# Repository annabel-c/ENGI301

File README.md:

# ENGI301

Repository for ENGI301 coursework

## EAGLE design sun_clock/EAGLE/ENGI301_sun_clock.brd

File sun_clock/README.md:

# PCB: PocketBeagle Sun Clock
Clock that shows the position of the sun and has a screen display of time; alarm can be set through mode, hour, and minute buttons.
This is a PCB design based on the PocketBeagle Sun Clock. See "https://github.com/annabel-c/ENGI301/tree/master/project_01" for original project.

## Files
Schematic

Board/Layout

Gerbers

Bill-of-Materials

Additional Documentation

## Story
When times call for another alarm clock--why not build it yourself? Make it fun with your personal indoor sun and moon (great for a cloudy day!), and have the option to set an alarm through 3 simple buttons: mode, hour and minute.

## Overview

The TFT display shows the time. Time is set upon boot, in Central Standard Time. Hold down the mode button (blue) to set an alarm time with hour (yellow) and minute (red). Every press increments the respective parameter by 1. Press hour and minute buttons at the same time to toggle alarm on and off. The on state is indicated by a red border (replacing the original gray one) on the screen display. A buzzer will sound at the time of the alarm, lasting a few seconds and turning off automatically. The servo will rotate 180 degrees at 6 am and 6 pm, revealing the sun or moon representing daytime or nighttime, respectively.

## Instructions

#### Hardware

The main pin configurations are described below:

TFT screen - SPI0

RTC - I2C1

Servo - PWM0

Speaker - PWM1

Buttons - GPIO 64, 46, 48

### Software

For help getting started with a PocketBeagle, see https://beagleboard.org/getting-started. Before running the code, several libraries must be downloaded:

- Install the Adafruit_Blinka library by running the following in Cloud9 IDE

sudo pip3 install Adafruit_Blinka

(run "sudo apt-get install python-setuptools" and "sudo apt-get install python-dev" if the above throws an error)

and download the Adafruit CircuitPython Library Bundle at https://github.com/adafruit/Adafruit_CircuitPython_Bundle

- Follow the instructions at https://learn.adafruit.com/adafruit-2-dot-8-color-tft-touchscreen-breakout-v2/python-wiring-and-setup for installing the RGB Display Library, DejaVu TTF Font, and the Pillow Library

See the Hackster.io page for more details: https://www.hackster.io/annabel-chang/pocketbeagle-sun-clock-f72acc

In the process of coding, make sure to use python3 (instead of python) is and use the prefix "sudo" to resolve any permission issues.

With everything set up, running

sudo python3 sun_clock.py

in the current directory should produce the clock display and functions as described in the first section. An auto run is also set up for this project such that the file runs upon boot, given in run.sh.

A video demonstrating how the alarm works can be reached here: https://www.youtube.com/watch?v=hUiSdnFPSFs&feature=youtu.be

In the video, the current time is 03:22, the alarm is set to 03:23 by holding the mode button and pressing the minute button (not shown setting from the initial 00:00 due to time constraints), the alarm is turned on by pressing hour and minute together (screen border turns red), and wait.... the alarm begins beeping at the set time! The alarm eventually terminates and the gray screen border is restored.

## Future Work

The screen provides a great deal of potential and versatility for this project; a touchscreen controller can be added so that touchcreen buttons replace the physical one, or other modes such as photo galleries and temperature/humidity detection can be included within the clock.

Python code for RTC with PocketBeagle remains to be investigated, hence this iteration of this project relies on datetime for time information. Future iterations could focus more on user-setting time and mode changes.

In addition, to become a more finished, stand-alone product, the clock should have a battery instead of an USB cable, and an aesthetic casing or LED effects would put the finishing touches on it.

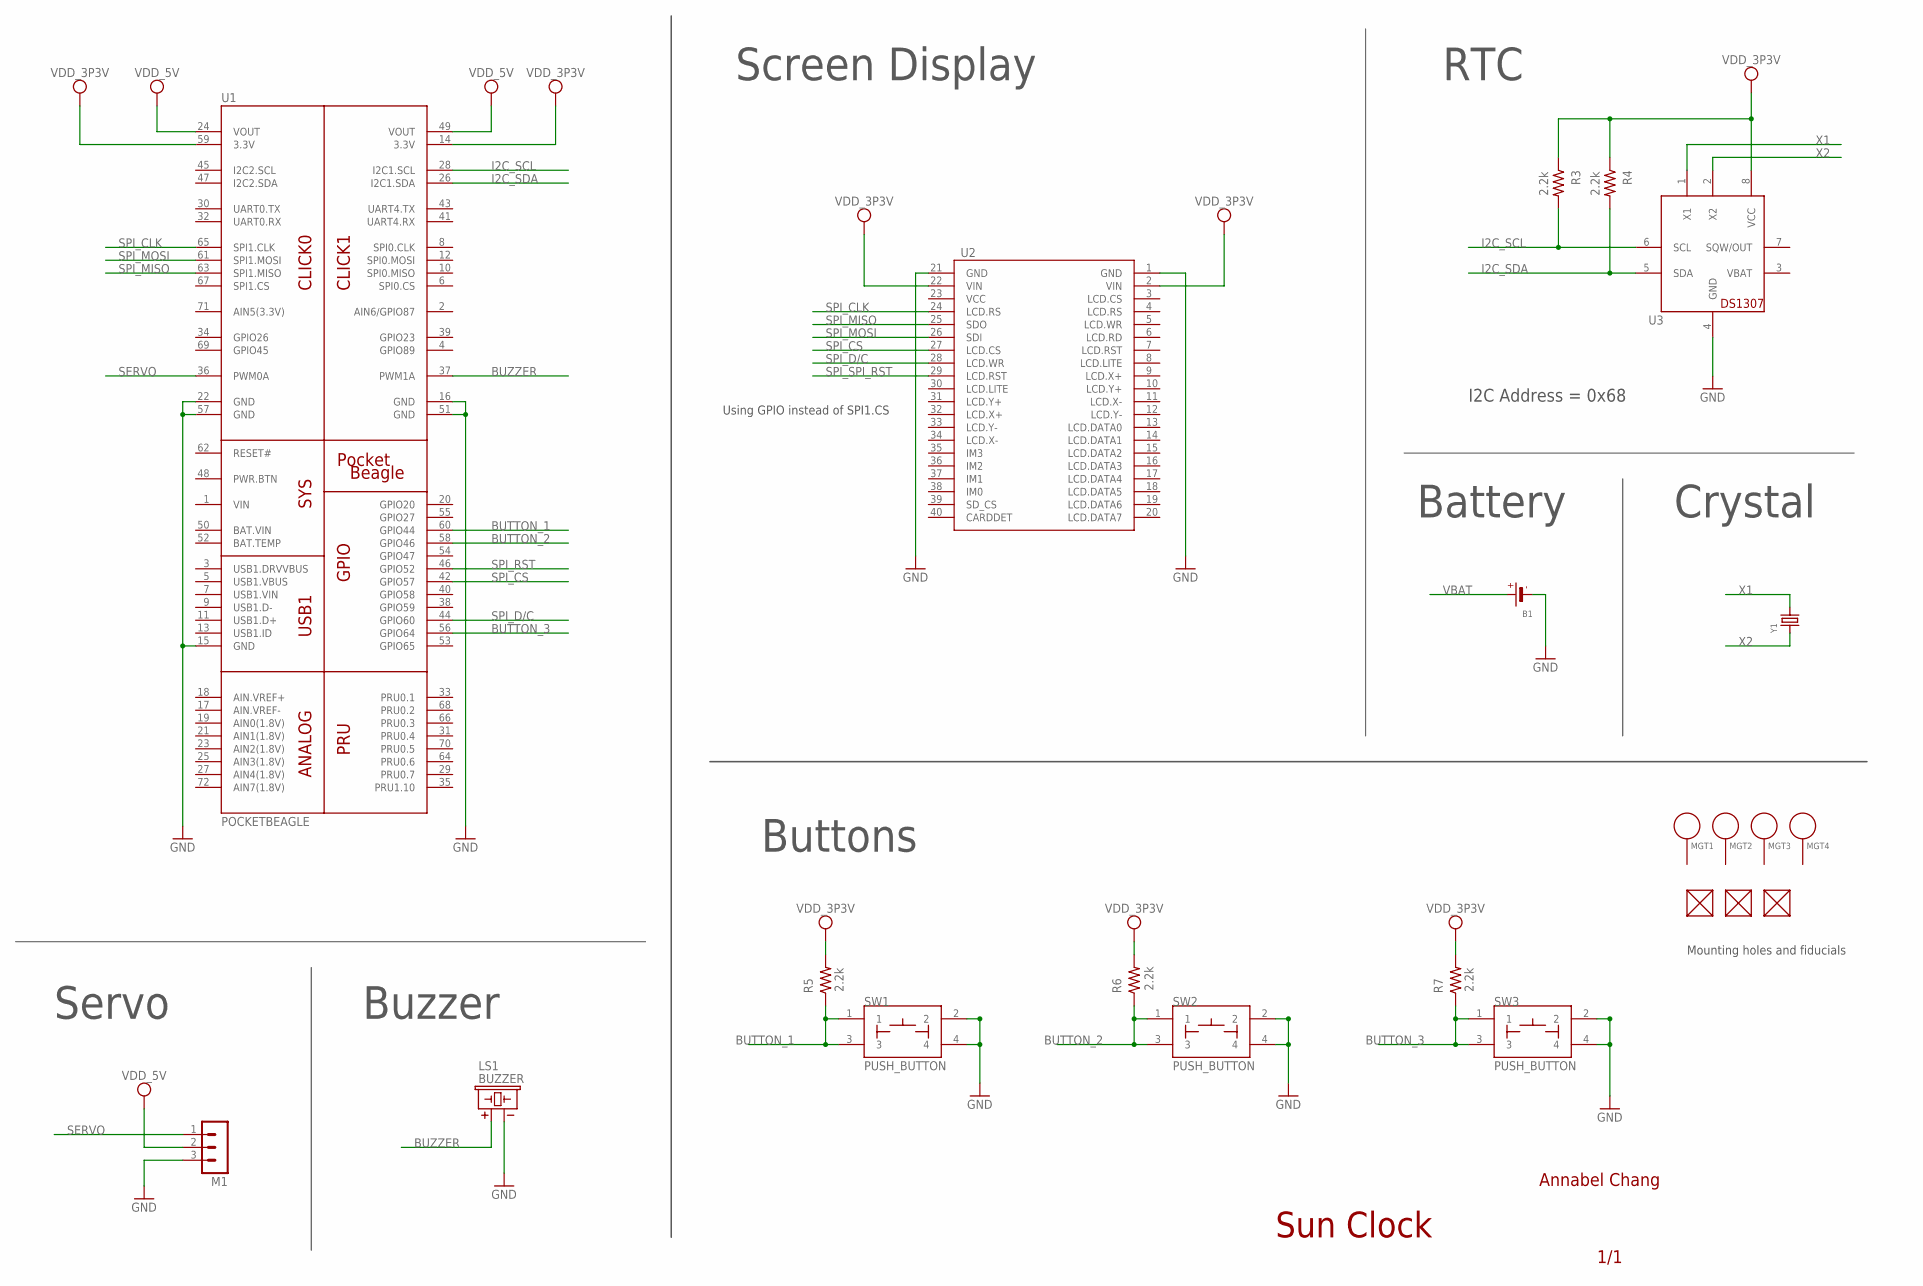
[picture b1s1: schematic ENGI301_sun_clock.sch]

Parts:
B1: BATTERYCR1220_SMT; CR1220
FUD1, FUD2, FUD3: FIDUCIAL; FIDUCIAL_40MIL
LS1: BUZZER; BUZZER_6.5MM
M1: MA03-1
MGT1, MGT2, MGT3, MGT4: MOUNTING_HOLE
R3, R4: 2.2k; R0805
R5, R6, R7: 2.2k; R0603
SW1, SW2, SW3: PUSH_BUTTON; BUTTON_12.5MM
U1: POCKETBEAGLE
U2: DISP_LCD_2.8IN
U3: DS1307; DIL08
Y1: CRYSTAL8.0X3.8; CRYSTAL_8X3.8

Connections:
BAT.VIN: U1.50 (BAT.VIN)
BUTTON_1: R5.1, SW1.1, SW1.3, U1.60 (GPIO44)
BUTTON_2: R6.1, SW2.1, SW2.3, U1.58 (GPIO46)
BUTTON_3: R7.1, SW3.1, SW3.3, U1.56 (GPIO64)
BUZZER: LS1.+, U1.37 (PWM1A)
GND: B1.-, LS1.-, M1.3, SW1.2, SW1.4, SW2.2, SW2.4, SW3.2, SW3.4, U1.15 (GND), U1.16 (GND), U1.22 (GND), U1.51 (GND), U1.57 (GND), U2.1 (GND), U2.21 (GND), U3.4 (GND)
I2C_SCL: R3.2, U1.28 (I2C1.SCL), U3.6 (SCL)
I2C_SDA: R4.2, U1.26 (I2C1.SDA), U3.5 (SDA)
SERVO: M1.1, U1.36 (PWM0A)
SPI_CLK: U1.65 (SPI1.CLK), U2.24 (LCD.RS)
SPI_CS: U1.42 (GPIO57), U2.27 (LCD.CS)
SPI_D/C: U1.44 (GPIO60), U2.28 (LCD.WR)
SPI_MISO: U1.63 (SPI1.MISO), U2.25 (SDO)
SPI_MOSI: U1.61 (SPI1.MOSI), U2.26 (SDI)
SPI_RST: U1.46 (GPIO52)
SPI_SPI_RST: U2.29 (LCD.RST)
VBAT: B1.+$1 (+), U3.3 (VBAT)
VDD_3P3V: R3.1, R4.1, R5.2, R6.2, R7.2, U1.14 (3.3V), U1.59 (3.3V), U2.2 (VIN), U2.22 (VIN), U3.8 (VCC)
VDD_5V: M1.2, U1.24 (VOUT), U1.49 (VOUT)
VIN: U1.1 (VIN)
X1: U3.1 (X1), Y1.P$4 (2)
X2: U3.2 (X2), Y1.P$1 (1)

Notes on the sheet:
Buttons
Servo
Screen Display
RTC
Buzzer
I2C Address = 0x68
Using GPIO instead of SPI1.CS
Annabel Chang
1/1
Sun Clock
Battery
Crystal
Mounting holes and fiducials

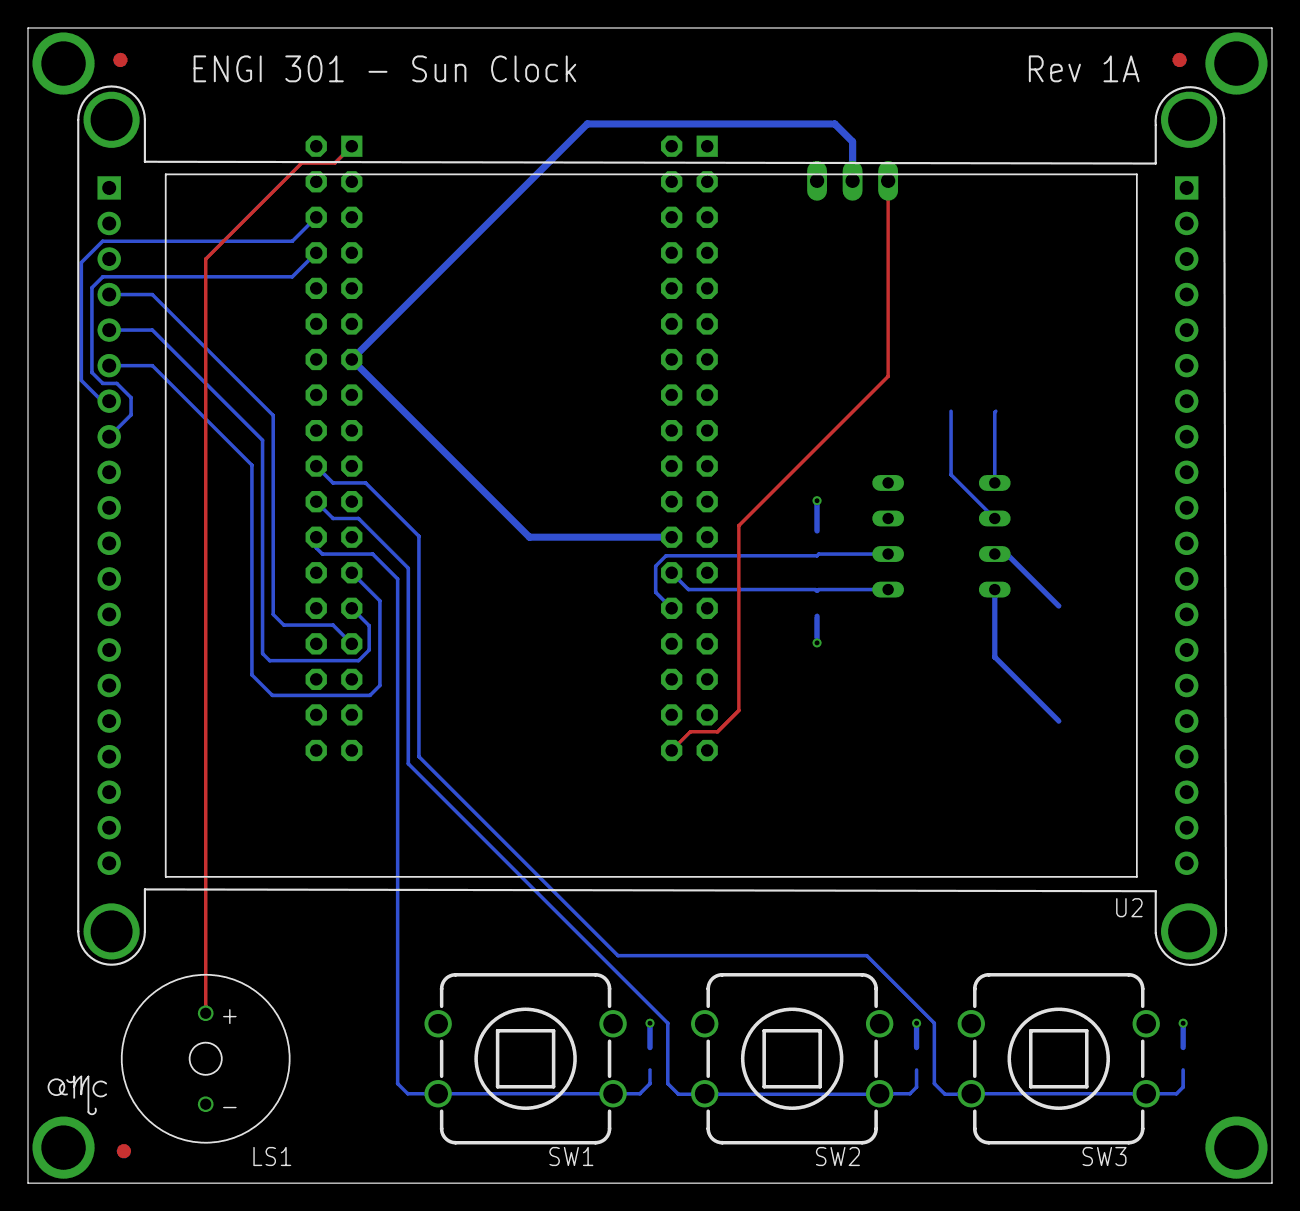
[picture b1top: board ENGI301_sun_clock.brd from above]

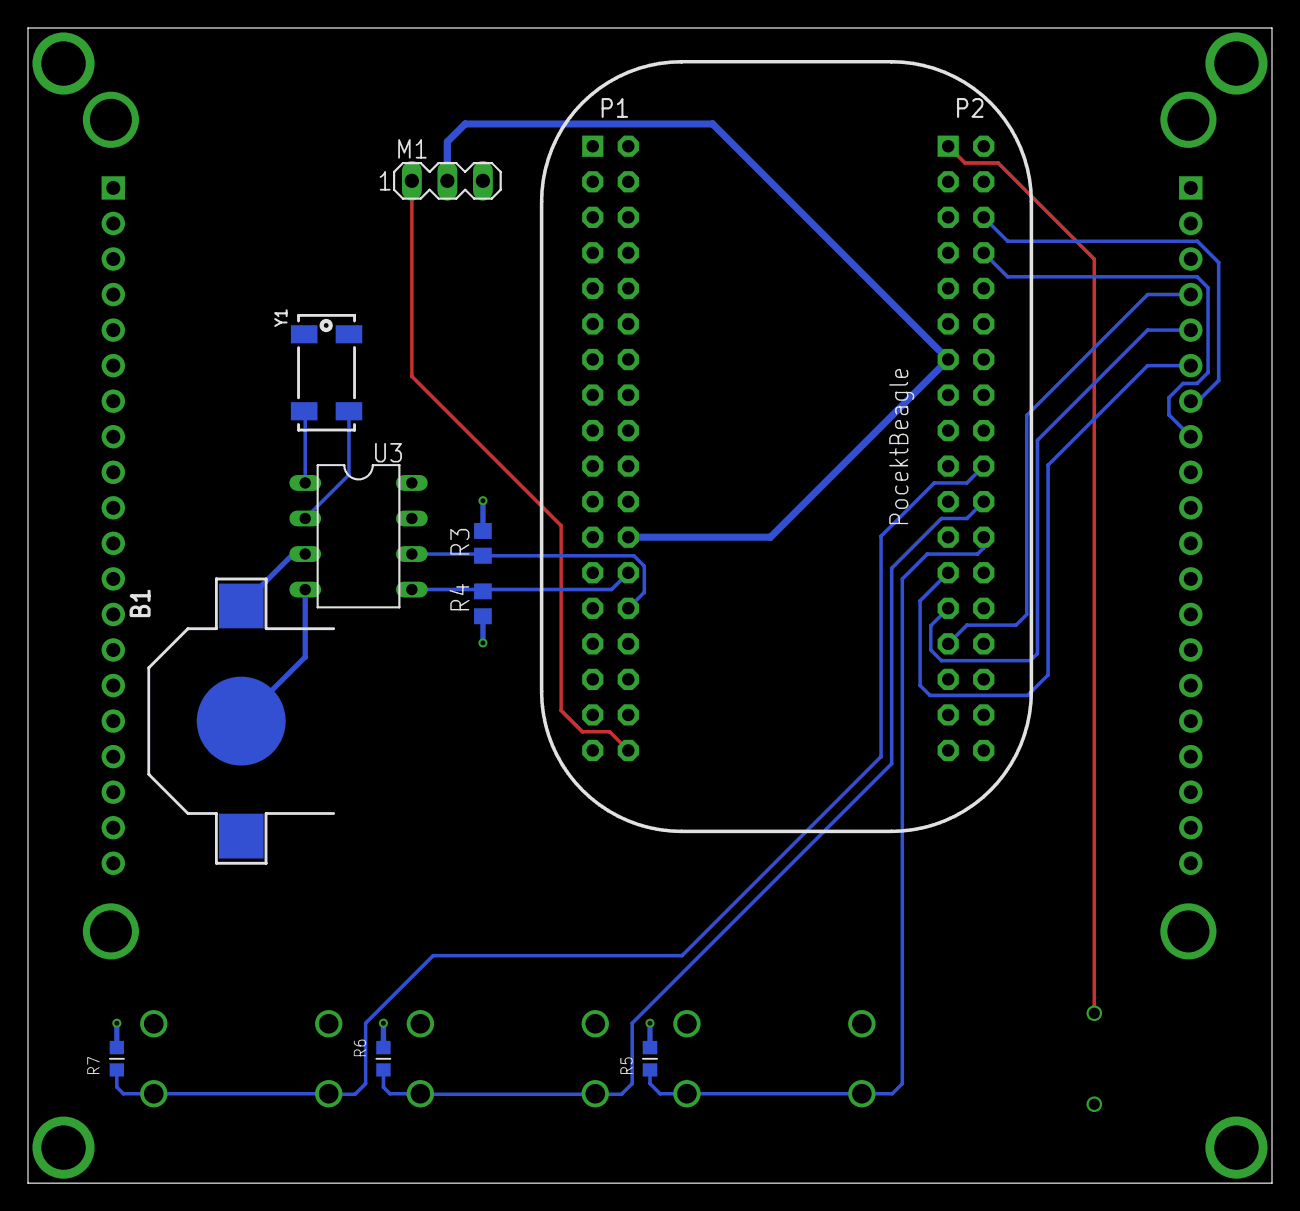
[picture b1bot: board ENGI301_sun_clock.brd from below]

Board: 4 copper layers, 88.9 x 82.5 mm, 22 parts (10 on the bottom side), 18 nets.

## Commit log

2019-09-18 Updating README.md
2019-10-07 Update simple_calc.py
    Added support for operators and Python 2
2019-10-07 Update simple_calc.py
    Convert inputs to int for lshift and rshift
2019-11-19 Create doc
2019-12-18 Create hi
2019-12-18 Create EAGLE
2019-12-18 Rename sun_clock/ENGI301_sun_clock.csv to sun_clock/docs/ENGI301_sun_clock.csv
